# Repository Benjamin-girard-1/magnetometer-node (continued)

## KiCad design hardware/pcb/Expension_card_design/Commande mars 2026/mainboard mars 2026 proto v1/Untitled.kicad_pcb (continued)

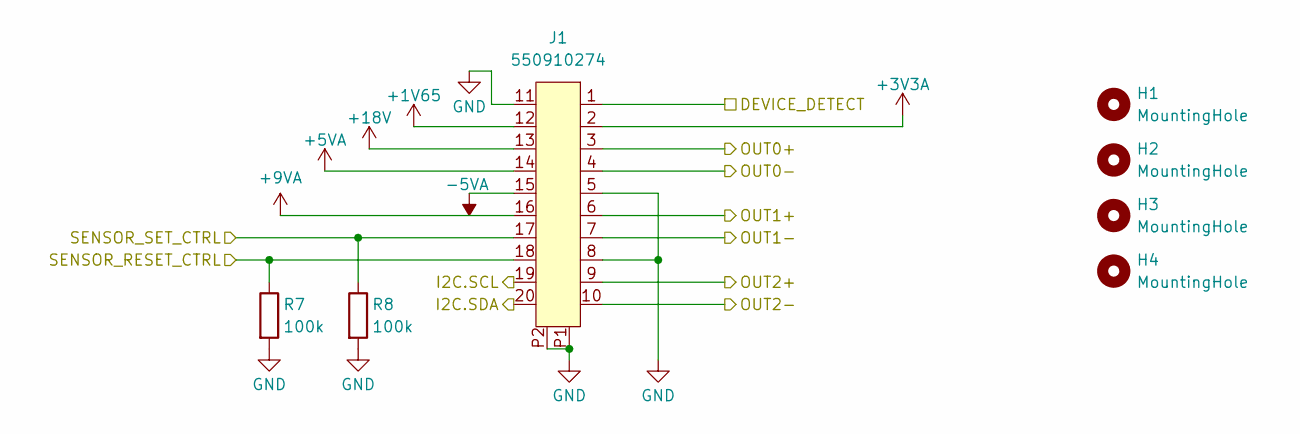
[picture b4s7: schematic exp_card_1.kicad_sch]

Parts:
H1, H2, H3, H4: MountingHole; MountingHole_4.3mm_M4
J1: 550910274; CON_550910274_MOL; LCSC C114095
R7, R8: 100k; R_0603_1608Metric; LCSC C25803

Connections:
+1V65: J1.12; also elsewhere on the board
+3V3A: J1.2; also elsewhere on the board
+5VA: J1.14; also elsewhere on the board
+9VA: J1.16; also elsewhere on the board
+18V: J1.13; also elsewhere on the board
-5VA: J1.15; also elsewhere on the board
/ADC_AD777x/AIN3+: J1.4; also elsewhere on the board
/ADC_AD777x/AIN3-: J1.3; also elsewhere on the board
/ADC_AD777x/AIN4+: J1.7; also elsewhere on the board
/ADC_AD777x/AIN4-: J1.6; also elsewhere on the board
/ADC_AD777x/AIN5+: J1.9; also elsewhere on the board
/ADC_AD777x/AIN5-: J1.10; also elsewhere on the board
/DEVICE_DETECT_2: J1.1; also elsewhere on the board
/RESET_2: J1.18, R7.1; also elsewhere on the board
/SCL_2: J1.19; also elsewhere on the board
/SDA_2: J1.20; also elsewhere on the board
/SET_2: J1.17, R8.1; also elsewhere on the board
GND: J1.5, J1.8, J1.11, J1.P1, J1.P2, R7.2, R8.2; also elsewhere on the board

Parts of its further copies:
H9, H10, H11, H12: MountingHole; MountingHole_4.3mm_M4
J3: 550910274; CON_550910274_MOL; LCSC C114095
R55, R56: 100k; R_0603_1608Metric; LCSC C25803

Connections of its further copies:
+1V65: J3.12; also elsewhere on the board
+3V3A: J3.2; also elsewhere on the board
+5VA: J3.14; also elsewhere on the board
+9VA: J3.16; also elsewhere on the board
+18V: J3.13; also elsewhere on the board
-5VA: J3.15; also elsewhere on the board
/ADC_AD777x/AIN0+: J3.3; also elsewhere on the board
/ADC_AD777x/AIN0-: J3.4; also elsewhere on the board
/ADC_AD777x/AIN1+: J3.7; also elsewhere on the board
/ADC_AD777x/AIN1-: J3.6; also elsewhere on the board
/ADC_AD777x/AIN2+: J3.10; also elsewhere on the board
/ADC_AD777x/AIN2-: J3.9; also elsewhere on the board
/DEVICE_DETECT_1: J3.1; also elsewhere on the board
/RESET_1: J3.18, R55.1; also elsewhere on the board
/SCL_1: J3.19; also elsewhere on the board
/SDA_1: J3.20; also elsewhere on the board
/SET_1: J3.17, R56.1; also elsewhere on the board
GND: J3.5, J3.8, J3.11, J3.P1, J3.P2, R55.2, R56.2; also elsewhere on the board

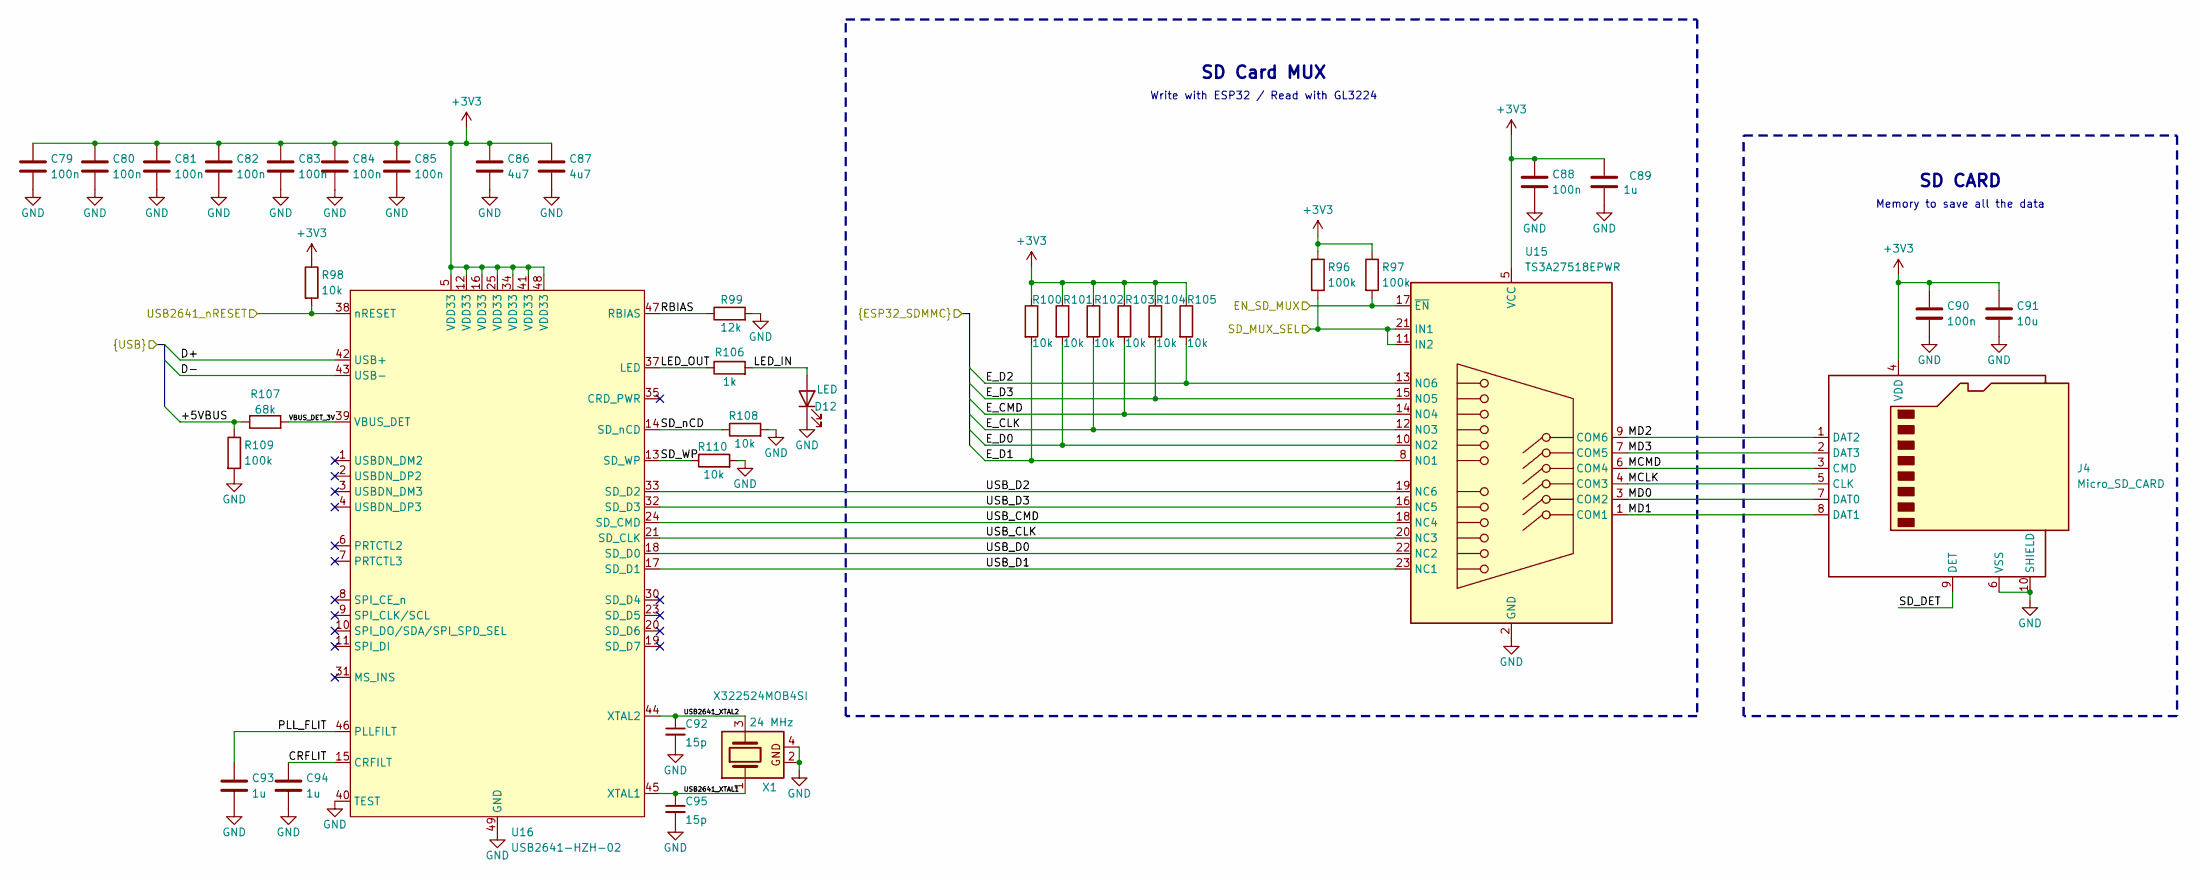
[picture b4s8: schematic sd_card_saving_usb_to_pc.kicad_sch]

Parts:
C79, C80, C81, C82, C83, C84, C85, C88, C90: 100n; C_0603_1608Metric; LCSC C14663
C86, C87: 4u7; C_1206_3216Metric; LCSC C29823
C89, C93, C94: 1u; C_0805_2012Metric; LCSC C28323
C91: 10u; C_0805_2012Metric; LCSC C15850
C92, C95: 15p; C_0603_1608Metric; LCSC C1644
D12: LED; LED_0805_2012Metric; LCSC C2296
J4: Micro_SD_CARD; CONN_503398-1892_MOL; LCSC C428492
R96, R97, R109: 100k; R_0603_1608Metric; LCSC C25803
R98, R100, R101, R102, R103, R104, R105, R108, R110: 10k; R_0603_1608Metric; LCSC C25804
R99: 12k; R_0603_1608Metric; LCSC C22790
R106: 1k; R_0603_1608Metric; LCSC C21190
R107: 68k; R_0603_1608Metric; LCSC C23231
U15: TS3A27518EPWR; TSSOP-24_4.4x7.8mm_P0.65mm; LCSC C2651937
U16: USB2641-HZH-02; QFN-48-1EP_7x7mm_P0.5mm_EP5.3x5.3mm; LCSC C633596
X1: X322524MOB4SI; Crystal_SMD_3225-4Pin_3.2x2.5mm; LCSC C70590

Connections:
+3V3: C79.1, C80.1, C81.1, C82.1, C83.1, C84.1, C85.1, C86.1, C87.1, C88.1, C89.2, C90.1, C91.1, J4.4 (VDD), R96.1, R97.1, R98.1, R100.1, R101.1, R102.1, R103.1, R104.1, R105.1, U15.5 (VCC), U16.5 (VDD33), U16.12 (VDD33), U16.16 (VDD33), U16.25 (VDD33), U16.34 (VDD33), U16.41 (VDD33), U16.48 (VDD33); also elsewhere on the board
/DATA_SAVING/+5VBUS: R107.1, R109.1; also elsewhere on the board
/DATA_SAVING/CRFLIT: C94.1, U16.15 (CRFILT)
/DATA_SAVING/D+: U16.42 (USB+); also elsewhere on the board
/DATA_SAVING/D-: U16.43 (USB-); also elsewhere on the board
/DATA_SAVING/EN_SD_MUX: R97.2, U15.17 (~EN); also elsewhere on the board
/DATA_SAVING/E_CLK: R102.2, U15.12 (NO3); also elsewhere on the board
/DATA_SAVING/E_CMD: R103.2, U15.14 (NO4); also elsewhere on the board
/DATA_SAVING/E_D0: R101.2, U15.10 (NO2); also elsewhere on the board
/DATA_SAVING/E_D1: R100.2, U15.8 (NO1); also elsewhere on the board
/DATA_SAVING/E_D2: R105.2, U15.13 (NO6); also elsewhere on the board
/DATA_SAVING/E_D3: R104.2, U15.15 (NO5); also elsewhere on the board
/DATA_SAVING/LED_IN: D12.2 (A), R106.2
/DATA_SAVING/LED_OUT: R106.1, U16.37 (LED)
/DATA_SAVING/MCLK: J4.5 (CLK), U15.4 (COM3)
/DATA_SAVING/MCMD: J4.3 (CMD), U15.6 (COM4)
/DATA_SAVING/MD0: J4.7 (DAT0), U15.3 (COM2)
/DATA_SAVING/MD1: J4.8 (DAT1), U15.1 (COM1)
/DATA_SAVING/MD2: J4.1 (DAT2), U15.9 (COM6)
/DATA_SAVING/MD3: J4.2 (DAT3), U15.7 (COM5)
/DATA_SAVING/PLL_FLIT: C93.1, U16.46 (PLLFILT)
/DATA_SAVING/RBIAS: R99.1, U16.47 (RBIAS)
/DATA_SAVING/SD_DET: J4.9 (DET)
/DATA_SAVING/SD_MUX_SEL: R96.2, U15.11 (IN2), U15.21 (IN1); also elsewhere on the board
/DATA_SAVING/SD_WP: R110.1, U16.13 (SD_WP)
/DATA_SAVING/SD_nCD: R108.1, U16.14 (SD_nCD)
/DATA_SAVING/USB2641_XTAL1: C95.1, U16.45 (XTAL1), X1.1
/DATA_SAVING/USB2641_XTAL2: C92.1, U16.44 (XTAL2), X1.3
/DATA_SAVING/USB2641_nRESET: R98.2, U16.38 (nRESET); also elsewhere on the board
/DATA_SAVING/USB_CLK: U15.20 (NC3), U16.21 (SD_CLK)
/DATA_SAVING/USB_CMD: U15.18 (NC4), U16.24 (SD_CMD)
/DATA_SAVING/USB_D0: U15.22 (NC2), U16.18 (SD_D0)
/DATA_SAVING/USB_D1: U15.23 (NC1), U16.17 (SD_D1)
/DATA_SAVING/USB_D2: U15.19 (NC6), U16.33 (SD_D2)
/DATA_SAVING/USB_D3: U15.16 (NC5), U16.32 (SD_D3)
/DATA_SAVING/VBUS_DET_3V: R107.2, U16.39 (VBUS_DET)
GND: C79.2, C80.2, C81.2, C82.2, C83.2, C84.2, C85.2, C86.2, C87.2, C88.2, C89.1, C90.2, C91.2, C92.2, C93.2, C94.2, C95.2, D12.1 (K), J4.6 (VSS), J4.10 (SHIELD), J4.11 (VSS), J4.12 (VSS), J4.13 (VSS), J4.14 (VSS), R99.2, R108.2, R109.2, R110.2, U15.2 (GND), U16.40 (TEST), U16.49 (GND), X1.2, X1.4; also elsewhere on the board

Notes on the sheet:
SD CARD
SD Card MUX
Memory to save all the data
Write with ESP32 / Read with GL3224

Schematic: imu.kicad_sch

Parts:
C96, C97, C98, C99, C100, C101: 100n; C_0603_1608Metric; LCSC C14663
TP3, TP4: TestPoint; TestPoint_THTPad_1.0x1.0mm_Drill0.5mm; not fitted
U17: SCL3300-D01-10; SCL3300-D01-10_MUR; LCSC C3825395
U19: LSM6DSVETR; LGA-14_3x2.5mm_P0.5mm_LayoutBorder3x4y; LCSC C41785564

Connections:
+3V3: C96.2, C97.2, C100.2, C101.2, U17.4 (VDD), U17.9 (DVIO), U19.5 (VDD_IO), U19.8 (VDD); also elsewhere on the board
/IMU/CS_LSM: U19.12 (CS); also elsewhere on the board
/IMU/CS_SCL: U17.5 (CS); also elsewhere on the board
/IMU/MISO: U17.6 (MISO), U19.1 (SDO); also elsewhere on the board
/IMU/MOSI: U17.7 (MOSI), U19.14 (SDA); also elsewhere on the board
/IMU/SCLK: U17.8 (SCK), U19.13 (SCL); also elsewhere on the board
GND: C96.1, C97.1, C98.1, C99.1, C100.1, C101.1, U17.1 (AVSS), U17.3 (RESERVED), U17.11 (DVSS), U17.12 (EMC_GND), U19.2 (SDx), U19.3 (SCx), U19.6 (GND), U19.7 (GND); also elsewhere on the board
unnamed: C99.2, U17.2 (A_EXTC)
unnamed: C98.2, U17.10 (D_EXTC)
unnamed: TP4.1, U19.4 (INT1)
unnamed: TP3.1, U19.9 (INT2)

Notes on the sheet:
Inertial Measurement Unit (IMU)
To know the orientation of the device

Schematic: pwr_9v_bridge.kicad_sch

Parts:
C4: 22p; C_0603_1608Metric; LCSC C1653
C5: 1u; C_0805_2012Metric; LCSC C28323
C6, C9, C10: 4u7; C_1206_3216Metric; LCSC C29823
C7: 10u; C_0805_2012Metric; LCSC C15850
C8: 100n; C_0603_1608Metric; LCSC C14663
D2: SS34; D_SMA; LCSC C8678
L2: 10u; L_Sunlord_MWSA0503S; LCSC C177248
R9, R10, R11, R15: 0; R_1206_3216Metric; LCSC C17888; not fitted
R12: 510k; R_0603_1608Metric; LCSC C23192
R13: 1k; R_0603_1608Metric; LCSC C21190
R14: 200k; R_0603_1608Metric; LCSC C25811
R16: 90k9; R_1206_3216Metric; LCSC C870933
R17: 100k; R_0603_1608Metric; LCSC C25803
TP13, TP14: TestPoint; TestPoint_THTPad_1.0x1.0mm_Drill0.5mm; not fitted
U2: LT3042xMSE; MSOP-10-1EP_3x3mm_P0.5mm_EP1.68x1.88mm; LCSC C580009
U3: TPS61040DBV; SOT-23-5; LCSC C7722

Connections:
+5V: R15.1; also elsewhere on the board
+9VA: R11.2; also elsewhere on the board
/MCU_ESP32S3/EN_BST_10V: U3.4 (EN); also elsewhere on the board
/PWR_9V_BRIDGE/+5V_IN_BST: C10.1, L2.1, R15.2, U3.5 (VIN)
/PWR_9V_BRIDGE/+9V_LDO_OUT: C6.1, R11.1, TP14.1, U2.9 (OUTS), U2.10 (OUT)
/PWR_9V_BRIDGE/+10V: R9.2, R10.1; also elsewhere on the board
/PWR_9V_BRIDGE/+10V_LDO_IN: C7.1, C8.1, R10.2, U2.1 (IN), U2.2 (IN), U2.3 (EN/UV), U2.6 (PGFB)
/PWR_9V_BRIDGE/+10V_OUT: C4.1, C5.1, D2.1 (K), R9.1, R12.1, TP13.1
/PWR_9V_BRIDGE/BST_10V_FB: C4.2, R14.2, R17.1, U3.3 (FB)
/PWR_9V_BRIDGE/BST_10V_FB_DIV: R12.2, R14.1
/PWR_9V_BRIDGE/BST_10V_SW: D2.2 (A), L2.2, U3.1 (SW)
/PWR_9V_BRIDGE/LDO_9V_ILIM: R13.2, U2.5 (ILIM)
/PWR_9V_BRIDGE/LDO_9V_SET: C9.1, R16.1, U2.7 (SET)
GND: C5.2, C6.2, C7.2, C8.2, C9.2, C10.2, R13.1, R16.2, R17.2, U2.8 (GND), U2.11 (GND), U3.2 (GND); also elsewhere on the board

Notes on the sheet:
Voltage for bridge of the magnetic sensors
+9V LDO
Voltage for the +9V and +5V LDO
+10V Boost

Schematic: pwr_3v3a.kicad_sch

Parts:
C32, C35: 4u7; C_1206_3216Metric; LCSC C29823
C33, C34: 100n; C_0603_1608Metric; LCSC C14663
FB1: FerriteBead; L_0603_1608Metric; LCSC C14709
R53, R54: 0; R_1206_3216Metric; LCSC C17888; not fitted
TP12: TestPoint; TestPoint_THTPad_1.0x1.0mm_Drill0.5mm; not fitted
U10: TPS7A2033PDBVR; SOT-23-5; LCSC C2862740

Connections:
+3V3A: R54.2; also elsewhere on the board
+5V: R53.1; also elsewhere on the board
/MCU_ESP32S3/EN_LDO_3V3: U10.3 (EN); also elsewhere on the board
/PWR_3V3A/+5V_IN: FB1.1, R53.2
/PWR_3V3A/LDO_3V3_IN: C32.1, C33.1, FB1.2, U10.1 (IN)
/PWR_3V3A/LDO_3V3_OUT: C34.1, C35.1, R54.1, TP12.1, U10.5 (OUT)
GND: C32.2, C33.2, C34.2, C35.2, U10.2 (GND), U10.4 (NC); also elsewhere on the board

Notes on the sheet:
+3.3V LDO
Voltage for analog domain of the ADC

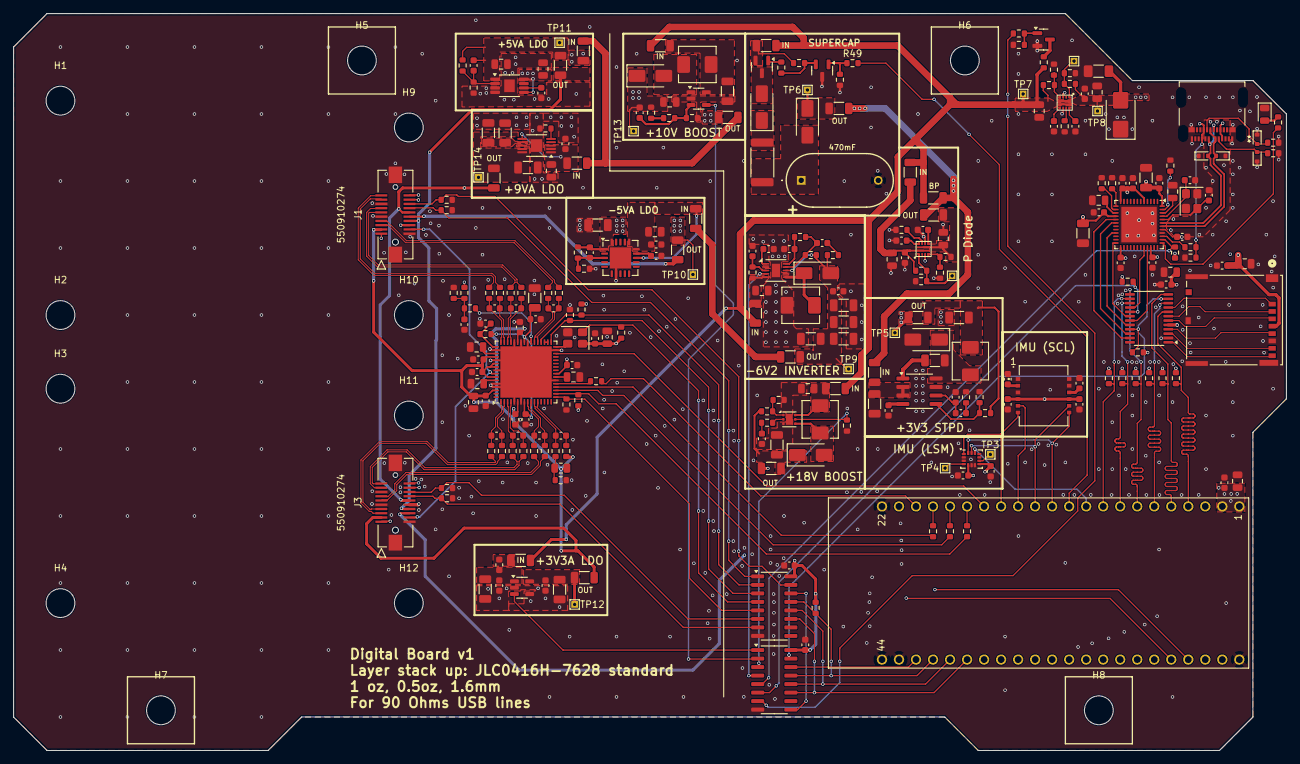
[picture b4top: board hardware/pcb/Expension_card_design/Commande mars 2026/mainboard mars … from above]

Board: 4 copper layers, 190.0 x 110.0 mm, 282 parts (0 on the bottom side), 191 nets.

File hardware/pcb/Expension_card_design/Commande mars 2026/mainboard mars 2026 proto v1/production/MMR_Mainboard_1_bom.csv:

Designator,Footprint,Quantity,Value,LCSC Part #
"C1, C13, C17, C23, C36, C51, C60, C62, C66, C7, C72, C91",0805,12,10u,C15850
"C10, C2, C32, C35, C6, C74, C75, C76, C77, C86, C87, C9",1206,12,4u7,C29823
"C100, C101, C11, C12, C14, C16, C21, C33, C34, C37, C38, C39, C40, C41, C42, C43, C50, C53, C54, C56, C64, C67, C71, C79, C8, C80, C81, C82, C83, C84, C85, C88, C90, C96, C97, C98, C99",0603,37,100n,C14663
"C15, C20, C5, C57, C58, C59, C89, C93, C94",0805,9,1u,C28323
"C18, C28, C29, C3, C61, C63, C68, C73",0603,8,10n,C57112
"C19, C30, C44, C45, C47, C48, C49, C52",0603,8,1n,C1588
"C22, C24",1206,2,22u,C12891
"C25, C55, C69",1206,3,47u,C96123
"C26, C78",0603,2,4n7,C53987
"C27, C70",0603,2,10p,C1634
C4,0603,1,22p,C1653
"C46, C65",0603,2,220n,C21120
"C92, C95",0603,2,15p,C1644
"D1, D10, D11, D2, D8, D9",D_SMA,6,SS34,C8678
D12,0805,1,LED,C2296
D3,D_SMB,1,P6SMB6.8CA,C7420377
"D4, D5, D6, D7",D_SOD-523,4,H5VUD5BB,C20615820
FB1,0603,1,FerriteBead,C14709
"J1, J3",CON_550910274_MOL,2,550910274,C114095
J2,CONN_201267-0005_MOL,1,USB_C_RECEPTACLE_MOLEX,C565324
J4,CONN_503398-1892_MOL,1,Micro_SD_CARD,C428492
"L1, L2, L3, L4",L_Sunlord_MWSA0503S,4,10u,C177248
"Q1, Q3",SOT-23,2,AO3400A,C20917
Q2,SOT-23,1,AO3401A,C15127
"R100, R101, R102, R103, R104, R105, R108, R110, R18, R43, R5, R61, R98",0603,13,10k,C25804
"R106, R13, R58, R65, R69, R81",0603,6,1k,C21190
R107,0603,1,68k,C23231
"R109, R17, R23, R32, R38, R4, R52, R55, R56, R59, R7, R73, R76, R78, R8, R80, R88, R91, R94, R96, R97",0603,21,100k,C25803
"R12, R93",0603,2,510k,C23192
"R14, R24, R40",0603,3,200k,C25811
R16,1206,1,90k9,C870933
"R19, R20, R21, R60, R62, R63, R64, R66, R68, R70, R71, R72, R74, R75, R77, R79",0603,16,22,C23345
"R22, R37",0603,2,470k,C23178
"R25, R41, R47, R84",0603,4,39k,C23153
"R27, R45",0603,2,2k,C22975
"R28, R29",0603,2,5k1,C23186
R3,0603,1,49k9,C23184
"R30, R31, R48, R49",0603,4,100,C22775
R42,0603,1,75k,C23242
R44,0603,1,24k,C23352
R50,2512,1,22,C2974113
R57,0603,1,300k,C23024
R6,0603,1,3k6,C22980
R67,0805,1,27k,C17526
"R85, R99",0603,2,12k,C22790
R89,0603,1,330k,C23137
R90,0603,1,10,C22859
TH1,0603,1,NCU18XH103D6SRB,C3154835
U1,WSON-6-1EP_2x2mm_P0.65mm_EP1x1.6mm,1,TPS61170,C15163
U10,SOT-23-5,1,TPS7A2033PDBVR,C2862740
U11,QFN-64-1EP_9x9mm_P0.5mm_EP7.65x7.65mm,1,AD7779ACPZ,C398822
U12,HVSSOP-8-1EP_3x3mm_P0.65mm_EP1.57x1.89mm,1,TPS7A4901DGNR,C16430
U13,Texas_RGW0020A_VQFN-20-1EP_5x5mm_P0.65mm_EP3.15x3.15mm,1,TPS7A3301RGWR,C90082
U14,VSON-10-1EP_3x3mm_P0.5mm_EP1.2x2mm,1,TPS63700DRCR,C54792
U15,TSSOP-24_4.4x7.8mm_P0.65mm,1,TS3A27518ERTW,C2651937
U16,QFN-48-1EP_7x7mm_P0.5mm_EP5.3x5.3mm,1,USB2641-HZH-02,C633596
U17,SCL3300-D01-10_MUR,1,SCL3300-D01-10,C3825395
U19,LGA-14_3x2.5mm_P0.5mm_LayoutBorder3x4y,1,LSM6DSVETR,C41785564
U2,MSOP-10-1EP_3x3mm_P0.5mm_EP1.68x1.88mm,1,LT3042xMSE,C580009
U3,SOT-23-5,1,TPS61040DBV,C7722
"U4, U5",SOIC-16_3.9x9.9mm_P1.27mm,2,"74HC595D,118",C5947
"U7, U8",SMD_VQFN-HR-10,2,TPS25210LRPWR,C2861226
U9,SOIC-8_3.9x4.9mm_P1.27mm,1,TPS54331DR,C9865
X1,Crystal_SMD_3225-4Pin_3.2x2.5mm,1,X322524MOB4SI,C70590
Y1,Crystal_SMD_3225-4Pin_3.2x2.5mm,1,OT2JI-111-8.192M,C7425393

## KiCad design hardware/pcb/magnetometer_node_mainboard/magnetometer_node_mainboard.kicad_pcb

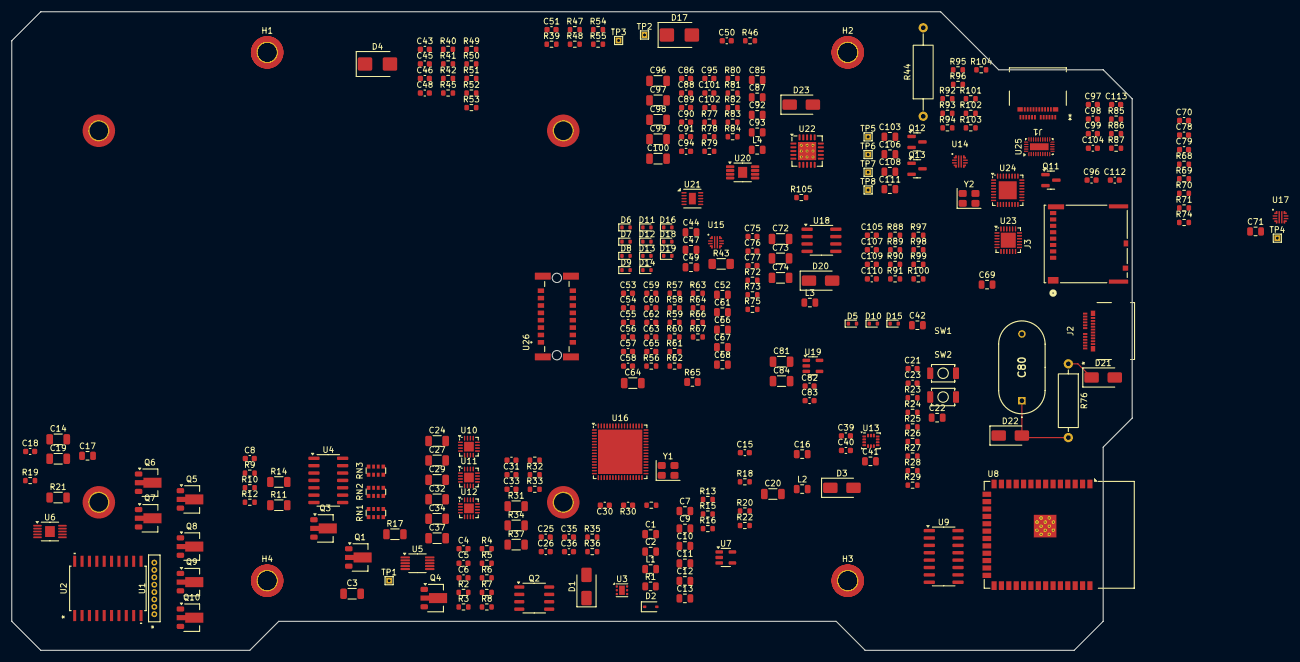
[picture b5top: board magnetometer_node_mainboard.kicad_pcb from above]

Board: 2 copper layers, 193.0 x 110.0 mm, 318 parts (0 on the bottom side), 220 nets.

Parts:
C1, C2, C7, C9, C10, C11, C12, C13, C17, C22, C41, C44, C49, C52, C61, C71, C85, C87, C92, C93, C106: 10u; C_0805_2012Metric
C3, C14, C19, C20, C24, C27, C29, C32, C34, C37, C81, C84, C97#2, C98, C99#2, C100: 4u7; C_1206_3216Metric
C4, C26, C31, C36, C62, C90: 220n; C_0603_1608Metric
C5, C46, C51, C79: 1n; C_0603_1608Metric
C6, C45, C50, C77, C78, C86, C88, C95: 10n; C_0603_1608Metric
C8, C18, C21, C23, C25, C28, C30, C33, C35, C38, C39, C40, C43, C48, C53, C54, C55, C56, C57, C58, C59, C60, C63, C65, C70, C82, C83, C89, C94, C96, C97, C98#2, C99, C102, C104, C105, C107, C109, C110: 100n; C_0603_1608Metric
C15: 22p; C_0603_1608Metric
C16, C42, C47, C66, C67, C68, C69, C103, C108, C111: 1u; C_0805_2012Metric
C64, C74, C96#2: 47u; C_1206_3216Metric
C72, C73: 22u; C_1206_3216Metric
C75, C91: 10p; C_0603_1608Metric
C76, C101: 4n7; C_0603_1608Metric
C80: 470mF; C_Radial_D8.0mm_P11.50mm
C112, C113: 18p; C_0603_1608Metric
D1, D3, D20, D21, D22, D23: SS34; D_SMA
D2: 1N4148WS; D_SOD-323
D4, D17: P6SMB6.8CA; D_SMB
D5, D6, D7, D8, D9, D10, D11, D12, D13, D14, D15, D16, D18, D19: H5VUD5BB; D_SOD-523
H1, H2, H3, H4, H5, H5#2, H6, H6#2, H7, H7#2, H8, H8#2: MountingHole_Pad; MountingHole_3.2mm_M3_DIN965_Pad_TopBottom
J1, J2: USB_C_RECEPTACLE_MOLEX; CONN_201267-0005_MOL
J3: Micro_SD_CARD; CONN_503398-1892_MOL
L1, L2, L3, L4: 10u; C_0805_2012Metric
Q1, Q4, Q5, Q7, Q9: D882; SOT-89-3
Q2: DMC3028LSD; SO-8_3.9x4.9mm_P1.27mm
Q3, Q6, Q8, Q10: B772; SOT-89-3
Q11, Q13: AO3400A; SOT-23
Q12: AO3401A; SOT-23
R1: 220; R_0805_2012Metric
R2, R4, R8, R30, R32, R33, R35, R36, R38, R59, R62, R64, R67: 1k; R_0603_1608Metric
R3: 49k9; R_0603_1608Metric
R5, R22, R40, R47, R53, R57, R60, R61, R63, R66, R69, R79, R82, R84, R89, R97, R98, R99, R100, R101, R103, R104: 100k; R_0603_1608Metric
R6, R23, R24, R28, R29, R73, R90, R91, R92, R93, R94: 10k; R_0603_1608Metric
R7: 3k6; R_0603_1608Metric
R9, R10, R12, R13, R15, R16, R51, R52, R86, R88: 100; R_0603_1608Metric
R11, R14, R17: 20; R_1206_3216Metric
R18, R81: 510k; R_0603_1608Metric
R19, R45, R50, R74, R95, R96: 2k; R_0603_1608Metric
R20, R41, R48, R70: 200k; R_0603_1608Metric
R21: 90k9; R_1206_3216Metric
R25, R26, R27, R56: 22; R_0603_1608Metric
R31, R34, R37: 48,7; R_1206_3216Metric
R39, R46, R68: 470k; R_0603_1608Metric
R42, R49, R71, R77, R85: 39k; R_0603_1608Metric
R43: R_1206_3216Metric_Pad1.30x1.75mm_HandSolder
R44: R_Axial_DIN0309_L9.0mm_D3.2mm_P15.24mm_Horizontal
R54, R55: 5k1; R_0603_1608Metric
R58: 300k; R_0603_1608Metric
R65: 2k4; R_0805_2012Metric
R72: 75k; R_0603_1608Metric
R75: 24k; R_0603_1608Metric
R76: 47; R_Axial_DIN0309_L9.0mm_D3.2mm_P12.70mm_Horizontal
R78: 12k; R_0603_1608Metric
R80: 10; R_0603_1608Metric
R83, R87: 330k; R_0603_1608Metric
R102: 680; R_0603_1608Metric
R105: 900k; R_0603_1608Metric
RN1, RN2, RN3: 10k; R_Array_Convex_4x0612
SW1, SW2: TS-1088-AR02016
TP1, TP2, TP3, TP4: TestPoint; TestPoint_THTPad_1.0x1.0mm_Drill0.5mm
TP5: GL3224_SPI_CS; TestPoint_THTPad_1.0x1.0mm_Drill0.5mm
TP6: GL3224_SPI_CK; TestPoint_THTPad_1.0x1.0mm_Drill0.5mm
TP7: GL3224_SPI_MISO; TestPoint_THTPad_1.0x1.0mm_Drill0.5mm
TP8: GL3224_SPI_MOSI; TestPoint_THTPad_1.0x1.0mm_Drill0.5mm
U1: HMC1001-RC; SIP8_HMC1001_HNW
U2: HMC1002-TR; SOIC20_HNW
U3: TPS61170; WSON-6-1EP_2x2mm_P0.65mm_EP1x1.6mm
U4: LM324; SOIC-14_3.9x8.7mm_P1.27mm
U5: MCP4728; MSOP-10_3x3mm_P0.5mm
U6: LT3042xMSE; MSOP-10-1EP_3x3mm_P0.5mm_EP1.68x1.88mm
U7: TPS61040DBV; SOT-23-5
U8: ESP32-S3-WROOM-1
U9: 74HC595D,118; SOIC-16_3.9x9.9mm_P1.27mm
U10, U11, U12: INA851RGTR; VQFN-16-1EP_3x3mm_P0.5mm_EP1.68x1.68mm
U13: ISM330DHCXTR; LGA-14_3x2.5mm_P0.5mm_LayoutBorder3x4y
U14, U15, U17: TPS25210LRPWR; VQFN-HR-10
U16: AD7779; QFN-64-1EP_9x9mm_P0.5mm_EP7.65x7.65mm
U18: TPS54331DR; SOIC-8_3.9x4.9mm_P1.27mm
U19: TPS7A2033PDBVR; SOT-23-5
U20: TPS7A4901DGNR; HVSSOP-8-1EP_3x3mm_P0.65mm_EP1.57x1.89mm
U21: TPS63700DRCR; VSON-10-1EP_3x3mm_P0.5mm_EP1.2x2mm
U22: TPS7A3301RGWR; Texas_RGW0020A_VQFN-20-1EP_5x5mm_P0.65mm_EP3.15x3.15mm_Ther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
U23: TS3A27518ERTW; WQFN-24-1EP_4x4mm_P0.5mm_EP2.6x2.6mm
U24: GL3224-OIY04; QFN-32-1EP_5x5mm_P0.5mm_EP3.1x3.1mm
U25: HD3SS3220RNHR; Texas_RNH0030A_WQFN-30-1EP_2.5x4.5mm_P0.4mm_EP1.2x3.2mm
U26: 2x08_pheonix_connector_male; GPS_TILE_3D
Y1: OT2JI-111-8.192M; Crystal_SMD_3225-4Pin_3.2x2.5mm
Y2: X322525MOB4SI; Crystal_SMD_3225-4Pin_3.2x2.5mm

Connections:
+1V65: U10.13 (VOCM), U11.13 (VOCM), U12.13 (VOCM), U16.57 (VCM)
+3V3: C21.1, C22.1, C23.1, C39.1, C40.1, C41.1, C58.1, C60.1, C61.1, C74.1, C105.1, C106.1, C107.1, C108.2, C109.1, J3.4 (VDD), L3.2, R23.1, R24.1, R28.2, R29.2, R63.1, R66.1, R72.1, R90.1, R91.1, R92.1, R93.1, R94.1, R95.1, R99.1, R100.1, R101.1, U8.2 (3V3), U9.16 (VCC), U13.5 (VDDIO), U13.8 (VDD), U13.12 (CS), U14.3 (PG), U15.3 (PG), U16.24 (IOVDD), U16.54 (FORMAT1), U16.55 (FORMAT0), U17.3 (PG), U23.5 (VCC), U25.8 (VCC33), U26.A1, U26.A2, U26.A3, U26.A4, Y1.4 (VDD)
+3V3A: C52.1, C53.1, C54.1, C55.1, C56.1, C57.1, C83.1, C84.1, R62.1, U10.16 (VCLAMP+), U11.16 (VCLAMP+), U12.16 (VCLAMP+), U16.6 (AVDD1A), U16.43 (AVDD1B), U16.52 (AVDD2B), U16.58 (AVDD2A), U16.62 (AVDD4), U19.1 (OUT)
+3V3D: C8.1, U5.1 (VDD)
+5V: C2.1, C20.1, C44.1, C49.1, C69.1, C70.1, C92.1, C110.1, C111.2, D21.2 (A), L1.1, L2.1, Q5.2, Q7.2, Q9.2, Q12.2 (S), R40.1, R47.1, R51.1, R68.1, R80.2, R85.1, U3.6 (VIN), U4.4 (V+), U7.5 (VIN), U14.6 (OUT), U15.6 (OUT), U17.5 (IN), U21.5 (IN), U25.30 (VDD5)
+5VA: C24.1, C25.1, C27.1, C28.1, C32.1, C33.1, C86.1, C87.1, R77.1, U10.14 (VS+), U11.14 (VS+), U12.14 (VS+), U20.1 (OUT)
+9VA: C14.1, R58.1, U1.7 (VBRIDGE), U2.4 (VBRIDGE(A)), U2.11 (VBRIDGE(B)), U6.9 (OUTS), U6.10 (OUT)
+18V: C3.1, D1.1 (K), R1.2, R3.1
-5VA: C29.1, C30.1, C34.1, C35.1, C37.1, C38.1, C95.1, C96#2.1, Q6.2, Q8.2, Q10.2, R83.1, U4.11 (V-), U10.7 (VS-), U11.7 (VS-), U12.7 (VS-), U22.1 (OUT), U22.20 (OUT)
/ADC_AD777X/ADC_9VA_MON: C59.1, R58.2, R59.1, R60.1
/ADC_AD777X/ADC_9VA_MON_FLT: R59.2, U16.39 (AIN6+)
/ADC_AD777X/ADC_AREG1CAP: C67.1, U16.59 (AREG1CAP)
/ADC_AD777X/ADC_AREG2CAP: C68.1, U16.51 (AREG2CAP)
/ADC_AD777X/ADC_CONVST_SAR: R57.1, U8.11 (IO18), U16.17 (CONVST_SAR)
/ADC_AD777X/ADC_DRDY: U8.39 (IO1), U16.30 (~DRDY)
/ADC_AD777X/ADC_DREGCAP: C66.1, U16.23 (DREGCAP)
/ADC_AD777X/ADC_MCLK: U16.32 (XTAL2/MCLK), Y1.3 (OUT)
/ADC_AD777X/ADC_MCLK_EN: R66.2, U8.36 (RXD0), Y1.1 (Tri-State)
/ADC_AD777X/ADC_REF+: C63.1, C64.1, R67.1, U16.8 (REF1+), U16.41 (REF2+)
/ADC_AD777X/ADC_REF_OUT: C65.1, R67.2, U16.49 (REF_OUT)
/ADC_AD777X/ADC_RESET: R63.2, U8.10 (IO17), U16.36 (~RESET)
/ADC_AD777X/ADC_SDO: R56.1, U16.21 (DCLK0/SDO)
/ADC_AD777X/ADC_START: R61.1, U8.37 (TXD0), U16.33 (~START)
/ADC_AD777X/PT1000_AIN+: C62.1, R62.2, U16.37 (AIN7+)
/ADC_AD777X/PT1000_AIN-: C62.2, R64.2, U16.38 (AIN7-)
/ADC_AD777X/PT1000_DRAIN: R64.1, R65.1
/ADC_AD777X/SPI.CS: R25.1, U16.18 (ALERT/~CS)
/ADC_AD777X/SPI.SCLK: R26.1, U16.19 (DCLK2/SCLK)
/ADC_AD777X/SPI.SDI: R27.1, U16.20 (DCLK1/SDI)
/ADC_AD777X/SPI.SDO: R56.2, U8.7 (IO7)
/ADC_AD777X/X_INA_OUT+: C26.1, R30.2, U16.2 (AIN0+)
/ADC_AD777X/X_INA_OUT-: C26.2, R32.2, U16.1 (AIN0-)
/ADC_AD777X/Y_INA_OUT+: C36.1, R36.2, U16.4 (AIN1+)
/ADC_AD777X/Y_INA_OUT-: C36.2, R38.2, U16.3 (AIN1-)
/ADC_AD777X/Z_INA_OUT+: C31.1, R33.2, U16.10 (AIN2+)
/ADC_AD777X/Z_INA_OUT-: C31.2, R35.2, U16.9 (AIN2-)
/ANALOG_FRONTEND_INA851/BR_X+: U2.2 (OUT+(A)), U10.1 (IN-)
/ANALOG_FRONTEND_INA851/BR_X-: U2.5 (OUT-(A)), U10.4 (IN+)
/ANALOG_FRONTEND_INA851/BR_Y+: U2.9 (OUT+(B)), U12.4 (IN+)
/ANALOG_FRONTEND_INA851/BR_Y-: U2.12 (OUT-(B)), U12.1 (IN-)
/ANALOG_FRONTEND_INA851/BR_Z+: U1.8 (OUT-), U11.4 (IN+)
/ANALOG_FRONTEND_INA851/BR_Z-: U1.5 (OUT+), U11.1 (IN-)
/ANALOG_FRONTEND_INA851/X_INA_PRE_AAF+: R30.1, U10.11 (OUT+)
/ANALOG_FRONTEND_INA851/X_INA_PRE_AAF-: R32.1, U10.10 (OUT-)
/ANALOG_FRONTEND_INA851/X_RG+: R31.1, U10.2 (RG+)
/ANALOG_FRONTEND_INA851/X_RG-: R31.2, U10.3 (RG-)
/ANALOG_FRONTEND_INA851/Y_INA_PRE_AAF+: R36.1, U12.11 (OUT+)
/ANALOG_FRONTEND_INA851/Y_INA_PRE_AAF-: R38.1, U12.10 (OUT-)
/ANALOG_FRONTEND_INA851/Y_RG+: R37.1, U12.2 (RG+)
/ANALOG_FRONTEND_INA851/Y_RG-: R37.2, U12.3 (RG-)
/ANALOG_FRONTEND_INA851/Z_INA_PRE_AAF+: R33.1, U11.11 (OUT+)
/ANALOG_FRONTEND_INA851/Z_INA_PRE_AAF-: R35.1, U11.10 (OUT-)
/ANALOG_FRONTEND_INA851/Z_RG+: R34.1, U11.2 (RG+)
/ANALOG_FRONTEND_INA851/Z_RG-: R34.2, U11.3 (RG-)
/DATA_SAVING/+5VBUS_DATA: C42.1, C43.1, D4.2 (A2), J1.A4 (VBUS), J1.A9 (VBUS), J1.B4 (VBUS), J1.B9 (VBUS), R39.1, R43.2, R44.1, R105.1, U14.5 (IN)
/DATA_SAVING/+5VBUS_DET: R105.2, U25.5 (VBUS_DET)
/DATA_SAVING/CC1: D6.2, J1.A5 (CC1), U25.2 (CC1)
/DATA_SAVING/CC2: D5.2, J1.B5 (CC2), U25.1 (CC2)
/DATA_SAVING/CLK: U8.32 (IO39), U23.22 (NC2)
/DATA_SAVING/CMD: U8.31 (IO38), U23.23 (NC1)
/DATA_SAVING/D0: U8.33 (IO40), U23.20 (NC3)
/DATA_SAVING/D1: U8.34 (IO41), U23.18 (NC4)
/DATA_SAVING/D2: U8.35 (IO42), U23.16 (NC5)
/DATA_SAVING/D3: U8.26 (IO45), U23.19 (NC6)
/DATA_SAVING/D+: D16.2, D19.2, J1.A6 (D+), J1.B6 (D+), J2.A6 (D+), J2.B6 (D+), U8.14 (USB_D+), U24.32 (DP)
/DATA_SAVING/D-: D15.2, D18.2, J1.A7 (D-), J1.B7 (D-), J2.A7 (D-), J2.B7 (D-), U8.13 (USB_D-), U24.31 (DM)
/DATA_SAVING/EN_SD_MUX: R98.1, U9.5 (QF), U23.17 (~EN)
/DATA_SAVING/EN_USB_READ: R88.1, R97.1, U9.6 (QG), U23.11 (IN2), U23.21 (IN1)
/DATA_SAVING/RX1+: D9.2, J1.B11 (RX1+), U25.15 (RX1p)
/DATA_SAVING/RX1-: D10.2, J1.B10 (RX1-), U25.14 (RX1n)
/DATA_SAVING/RX2+: D7.2, J1.A11 (RX2+), U25.18 (RX2p)
/DATA_SAVING/RX2-: D8.2, J1.A10 (RX2-), U25.19 (RX2n)
/DATA_SAVING/TX1+: D14.2, J1.A2 (TX1+), U25.17 (TX1p)
/DATA_SAVING/TX1-: D13.2, J1.A3 (TX1-), U25.16 (TX1n)
/DATA_SAVING/TX2+: D12.2, J1.B2 (TX2+), U25.21 (TX2p)
/DATA_SAVING/TX2-: D11.2, J1.B3 (TX2-), U25.20 (TX2n)
/GPS_TILE/GPS_NRESET: U9.4 (QE), U26.B1
/GPS_TILE/GPS_TIMEPULSE: U8.8 (IO15), U26.B2
/GPS_TILE/GPS_UART.RX: U8.16 (IO46), U26.B4
/GPS_TILE/GPS_UART.TX: U8.24 (IO47), U26.B5
/IMU/I2C.SCL: U5.2 (SCL), U8.38 (IO2), U13.13 (SCL)
/IMU/I2C.SDA: U5.3 (SDA), U8.4 (IO4), U13.14 (SDA)
/IMU/I2C.SDO: U8.15 (IO3), U13.1 (SDO/SA0)
/IO_CONNECTOR/+5VBUS_DEBUG: C47.1, C48.1, D17.2 (A2), J2.A4 (VBUS), J2.A9 (VBUS), J2.B4 (VBUS), J2.B9 (VBUS), R46.1, U15.5 (IN)
/IO_CONNECTOR/EN_KEEPALIVE: R52.1, U8.25 (IO48)
/IO_CONNECTOR/EN_KEEPALIVE_DRAIN: Q11.3 (D), R51.2
/IO_CONNECTOR/EN_KEEPALIVE_GATE: Q11.1 (G), R52.2, R53.1
/MCU_ESP32S3/ADC_SPI_CS: R25.2, U8.5 (IO5)
/MCU_ESP32S3/ADC_SPI_SCLK: R26.2, U8.6 (IO6)
/MCU_ESP32S3/ADC_SPI_SDI: R27.2, U8.12 (IO8)
/MCU_ESP32S3/DAC_LDAC_N: U5.4 (~LDAC), U9.7 (QH)
/MCU_ESP32S3/EN_BST_10V: U7.4 (EN), U9.15 (QA)
/MCU_ESP32S3/EN_BST_18V: R5.1, U3.5 (CTRL), U9.3 (QD)
/MCU_ESP32S3/EN_INV_-5V: U9.2 (QC), U21.4 (EN)
/MCU_ESP32S3/EN_LDO_3V3: U9.1 (QB), U19.3 (EN)
/MCU_ESP32S3/ESP32_BOOTH: R24.2, SW2.2, U8.27 (IO0)
/MCU_ESP32S3/ESP32_EN: R23.2, SW1.2, U8.3 (EN)
/MCU_ESP32S3/SENSOR_RESET_CTRL: Q2.2 (G1), U8.17 (IO9)
/MCU_ESP32S3/SENSOR_SET_CTRL: C5.1, R8.1, U8.18 (IO10)
/PWR_3V3A/LDO_3V3_IN: C81.1, C82.1, U19.4 (IN)
/PWR_3V3D/3V3D_EFUSE_DVDT: C79.1, U17.7 (dV/dt)
/PWR_3V3D/3V3D_EFUSE_EN_ULVO: R68.2, R70.1, TP4.1, U17.1 (EN/ULVO)
/PWR_3V3D/3V3D_EFUSE_ILM: R74.1, U17.9 (ILM)
/PWR_3V3D/3V3D_EFUSE_ITIMER: C78.1, U17.10 (ITIMER)
/PWR_3V3D/3V3D_EFUSE_PGTH: R69.2, R71.1, U17.4 (PGTH)
/PWR_3V3D/5V_CAP_CHG: D21.1 (K), R76.1
/PWR_3V3D/5V_HOLDUP: C71.1, C73.1, D22.1 (K), R69.1, U17.6 (OUT), U18.2 (VIN), U18.3 (EN)
/PWR_3V3D/5V_SUPERCAP: C80.1, D22.2 (A), R76.2
/PWR_3V3D/STPD_3V3_BOOT: C72.1, U18.1 (BOOT)
/PWR_3V3D/STPD_3V3_COMP: C75.1, R73.1, U18.6 (COMP)
/PWR_3V3D/STPD_3V3_COMP_F: C76.1, R73.2
/PWR_3V3D/STPD_3V3_PH: C72.2, D20.1 (K), L3.1, U18.8 (PH)
/PWR_3V3D/STPD_3V3_SS: C77.1, U18.4 (SS)
/PWR_3V3D/STPD_3V3_VSENS: R72.2, R75.1, U18.5 (VSENSE)
/PWR_5VA_NEG5/+10V: C15.1, C16.1, C17.1, C18.1, C85.1, D3.1 (K), R18.1, U6.1 (IN), U6.2 (IN), U6.3 (EN/UV), U6.6 (PGFB), U20.5 (EN), U20.8 (IN)
/PWR_5VA_NEG5/INV_N5V5_COMP: C101.1, U21.1 (COMP)
/PWR_5VA_NEG5/INV_N5V5_FB: C91.1, R79.2, R81.1, U21.9 (FB)
/PWR_5VA_NEG5/INV_N5V5_FF: C91.2, R82.1
/PWR_5VA_NEG5/INV_N5V5_SW: D23.1 (K), L4.1, U21.6 (SW)
/PWR_5VA_NEG5/INV_N5V5_VIN: C89.1, R80.1, U21.3 (VIN)
/PWR_5VA_NEG5/INV_N5V5_VREF: C90.1, R79.1, U21.10 (VREF)
/PWR_5VA_NEG5/LDO_N5V_FB: C95.2, R83.2, R84.1, U22.3 (FB)
/PWR_5VA_NEG5/LDO_N5V_NR: C102.1, U22.14 (NR/SS)
/PWR_5VA_NEG5/LDO_P5V_FB: C86.2, R77.2, R78.1, U20.2 (FB)
/PWR_5VA_NEG5/LDO_P5V_NR: C88.1, U20.6 (NR/SS)
/PWR_5VA_NEG5/N5V5_PRE_N5VA: C93.1, C94.1, C97#2.1, C98.1, C99#2.1, C100.1, D23.2 (A), R81.2, R82.2, U21.8 (OUT), U22.13 (EN), U22.15 (IN), U22.16 (IN)
/PWR_9V_BRIDGE/BST_10V_FB: C15.2, R20.2, R22.1, U7.3 (FB)
/PWR_9V_BRIDGE/BST_10V_SW: D3.2 (A), L2.2, U7.1 (SW)
/PWR_9V_BRIDGE/LDO_9V_ILIM: R19.1, U6.5 (ILIM)
/PWR_9V_BRIDGE/LDO_9V_SET: C19.1, R21.1, U6.7 (SET)
/SENSOR_3AXIS_HMC100X/OFFSET_X+: C9.2, R11.2, RN1.5 (R4.2), U2.17 (OFFSET(+A))
/SENSOR_3AXIS_HMC100X/OFFSET_Y+: C12.2, R14.2, RN2.5 (R4.2), U2.15 (OFFSET+(B))
/SENSOR_3AXIS_HMC100X/OFFSET_Z+: C13.2, R17.2, RN3.5 (R4.2), U1.2 (OFFSET+)
/SENSOR_3AXIS_HMC100X/SETRESET_AFTER_1001: U1.3 (S/R-), U2.16 (S/R+(A))
/SENSOR_3AXIS_HMC100X/SETRESET_AFTER_1002A: U2.14 (S/R+(B)), U2.20 (S/R-(A))
/SENSOR_3AXIS_HMC100X/SETRESET_STRAP: C4.2, U1.1 (S/R+)
/SENSOR_OFFSET_DRIVERS/DAC_OUT_REF: RN1.1 (R1), RN2.1 (R1), RN3.1 (R1), U5.9 (VOUTD)
/SENSOR_OFFSET_DRIVERS/DAC_RDY_N: TP1.1, U5.5 (RDY/~BSY)
/SENSOR_OFFSET_DRIVERS/OFF_X_BN: Q5.1, R9.2
/SENSOR_OFFSET_DRIVERS/OFF_X_BP: Q6.1, R10.2
/SENSOR_OFFSET_DRIVERS/OFF_X_DRV: R9.1, R10.1, U4.1
/SENSOR_OFFSET_DRIVERS/OFF_X_INN: C9.1, RN1.3 (R2.2), U4.2 (-)
/SENSOR_OFFSET_DRIVERS/OFF_X_INP: C7.1, RN1.2 (R1.2), U4.3 (+)
/SENSOR_OFFSET_DRIVERS/OFF_X_SENSE_P: C7.2, Q5.3, Q6.3, R11.1, RN1.4 (R3.2)
/SENSOR_OFFSET_DRIVERS/OFF_Y_BN: Q7.1, R12.2
/SENSOR_OFFSET_DRIVERS/OFF_Y_BP: Q8.1, R13.2
/SENSOR_OFFSET_DRIVERS/OFF_Y_DRV: R12.1, R13.1, U4.7
/SENSOR_OFFSET_DRIVERS/OFF_Y_INN: C12.1, RN2.3 (R2.2), U4.6 (-)
/SENSOR_OFFSET_DRIVERS/OFF_Y_INP: C10.1, RN2.2 (R1.2), U4.5 (+)
/SENSOR_OFFSET_DRIVERS/OFF_Y_SENSE_P: C10.2, Q7.3, Q8.3, R14.1, RN2.4 (R3.2)
/SENSOR_OFFSET_DRIVERS/OFF_Z_BN: Q9.1, R15.2
/SENSOR_OFFSET_DRIVERS/OFF_Z_BP: Q10.1, R16.2
/SENSOR_OFFSET_DRIVERS/OFF_Z_DRV: R15.1, R16.1, U4.8
/SENSOR_OFFSET_DRIVERS/OFF_Z_INN: C13.1, RN3.3 (R2.2), U4.9 (-)
/SENSOR_OFFSET_DRIVERS/OFF_Z_INP: C11.1, RN3.2 (R1.2), U4.10 (+)
/SENSOR_OFFSET_DRIVERS/OFF_Z_SENSE_P: C11.2, Q9.3, Q10.3, R17.1, RN3.4 (R3.2)
/SENSOR_OFFSET_DRIVERS/UNUSED_LM324_CHD: U4.13 (-), U4.14
GND: C1.2, C2.2, C3.2, C6.2, C8.2, C14.2, C16.2, C17.2, C18.2, C19.2, C20.2, C21.2, C22.2, C23.2, C24.2, C25.2, C27.2, C28.2, C29.2, C30.2, C32.2, C33.2, C34.2, C35.2, C37.2, C38.2, C39.2, C40.2, C41.2, C42.2, C43.2, C44.2, C45.2, C46.2, C47.2, C48.2, C49.2, C50.2, C51.2, C52.2, C53.2, C54.2, C55.2, C56.2, C57.2, C58.2, C59.2, C60.2, C61.2, C63.2, C64.2, C65.2, C66.2, C67.2, C68.2, C69.2, C70.2, C71.2, C73.2, C74.2, C75.2, C76.2, C77.2, C78.2, C79.2, C80.2, C81.2, C82.2, C83.2, C84.2, C85.2, C87.2, C88.2, C89.2, C90.2, C92.2, C93.2, C94.2, C96.2, C96#2.2, C97.2, C97#2.2, C98.2, C98#2.2, C99.2, C99#2.2, C100.2, C101.2, C102.2, C103.1, C104.2, C105.2, C106.2, C107.2, C108.1, C109.2, C110.2, C111.1, C112.2, C113.2, D2.2 (A), D4.1 (A1), D5.1, D6.1, D7.1, D8.1, D9.1, D10.1, D11.1, D12.1, D13.1, D14.1, D15.1, D16.1, D17.1 (A1), D18.1, D19.1, D20.2 (A), H1.1, H2.1, H3.1, H4.1, H5#2.1, H6#2.1, H7#2.1, H8.1, J1.A1 (GND), J1.A12 (GND), J1.B1 (GND), J1.B12 (GND), J3.6 (VSS), J3.10 (SHIELD), J3.11 (VSS), J3.12 (VSS), J3.13 (VSS), J3.14 (VSS), L4.2, Q2.1 (S1), Q3.2, Q4.3 (E), Q11.2 (S), Q13.3 (D), R5.2, R7.2, R19.2, R21.2, R22.2, R41.2, R42.2, R43.1, R44.2, R45.2, R48.2, R49.2, R50.2, R53.2, R54.2, R55.2, R57.2, R60.2, R61.2, R65.2, R70.2, R71.2, R74.2, R75.2, R78.2, R84.2, R87.1, R89.2, R97.2, R98.2, R102.1, R103.2, R104.2, SW1.1, SW2.1, U1.4 (GND), U1.6 (OFFSET-), U2.1 (GND1(A)), U2.3 (OFFSET-(A)), U2.6 (GND2(A)), U2.7 (S/R-(B)), U2.8 (GND1(B)), U2.10 (OFFSET-(B)), U2.13 (GND2(B)), U2.18 (GND_PLN), U3.3 (GND), U3.7 (TP), U4.12 (+), U5.10 (VSS), U7.2 (GND), U8.1 (GND), U8.40 (GND), U8.41 (GND), U9.8 (GND), U10.5 (VCLAMP-), U10.17 (TP), U11.5 (VCLAMP-), U11.17 (TP), U12.5 (VCLAMP-), U12.17 (TP), U13.2 (SDx), U13.3 (SCx), U13.6 (GND), U13.7 (GND), U14.8 (GND), U15.8 (GND), U16.5 (AVSS1A), U16.7 (REF1-), U16.22 (DGND), U16.31 (XTAL1), U16.40 (AIN6-), U16.42 (REF2-), U16.44 (AVSS1B), U16.50 (AVSS2B), U16.53 (AVSS3), U16.56 (CLK_SEL), U16.60 (AVSS2A), U16.61 (AVSS4), U16.65 (EPAD(AVSSx)), U17.8 (GND), U18.7 (GND), U19.2 (GND), U19.5 (Pad), U20.3 (NC), U20.4 (GND), U20.9 (PwPd), U21.2 (GND), U21.7 (PSGND), U21.11 (PowerPAD), U22.7 (GND), U22.21 (EP), U23.2 (GND), U23.25 (GND), U24.27 (GND), U24.33 (GND), U25.4 (PORT), U25.12 (ENn_MUX), U25.13 (GND), U25.28 (GND), U25.29 (ENn_CC), U25.31 (GND), U26.A5, U26.A6, U26.A7, U26.A8, U26.B6, U26.B7, U26.B8, U26.MP1, U26.MP2, U26.MP3, U26.MP4, Y1.2 (GND), Y2.2, Y2.4
unnamed: C4.1, Q2.5 (D2), Q2.6 (D2), Q2.7 (D1), Q2.8 (D1)
unnamed: C6.1, R6.2
unnamed: C96.1, C97.1, C98#2.1, C99.1
unnamed: D1.2 (A), L1.2, U3.4 (SW)
unnamed: C5.2, D2.1 (K), Q4.1 (B), R8.2
unnamed: R96.1, U24.14 (LED)
unnamed: J2.A5 (CC1), R55.1
unnamed: J2.B5 (CC2), R54.1
unnamed: J2.A1 (GND), J2.A12 (GND), J2.B1 (GND), J2.B12 (GND)
unnamed: J3.5 (CLK), U23.3 (COM2)
unnamed: J3.3 (CMD), R94.2, U23.1 (COM1)
unnamed: J3.7 (DAT0), R93.2, U23.4 (COM3)
unnamed: J3.8 (DAT1), R92.2, U23.6 (COM4)
unnamed: J3.1 (DAT2), R91.2, U23.7 (COM5)
unnamed: J3.2 (DAT3), R90.2, U23.9 (COM6)
unnamed: Q1.1 (B), Q3.1, R2.2, R4.1
unnamed: C1.1, Q1.2 (C), Q2.3 (S2), R1.1, R2.1
unnamed: Q1.3 (E), Q2.4 (G2), Q3.3
unnamed: Q4.2 (C), R4.2
unnamed: C103.2, C104.1, Q12.3 (D), R87.2, U24.15 (VBUS)
unnamed: Q12.1 (G), R86.2
unnamed: Q13.1 (G), R88.2, R89.1
unnamed: Q13.2 (S), R85.2, R86.1
unnamed: R18.2, R20.1
unnamed: R6.1, U3.2 (COMP)
unnamed: R3.2, R7.1, U3.1 (FB)
unnamed: U6.8 (GND), U6.11 (GND)
unnamed: U8.19 (IO11), U9.14 (SER)
unnamed: U8.21 (IO13), U9.11 (SRCLK)
unnamed: U8.22 (IO14), U9.10 (~SRCLR)
unnamed: R29.1, U8.9 (IO16), U9.12 (RCLK)
unnamed: R28.1, U9.13 (~OE)
unnamed: R39.2, R41.1, TP2.1, U14.1 (EN/ULVO)
unnamed: R45.1, U14.9 (ILM)
unnamed: C45.1, U14.10 (ITIMER)
unnamed: R40.2, R42.1, U14.4 (PGTH)
unnamed: C46.1, U14.7 (dV/dt)
unnamed: R46.2, R48.1, TP3.1, U15.1 (EN/ULVO)
unnamed: R50.1, U15.9 (ILM)
unnamed: C50.1, U15.10 (ITIMER)
unnamed: R47.2, R49.1, U15.4 (PGTH)
unnamed: C51.1, U15.7 (dV/dt)
unnamed: U16.34 (~SYNC_OUT), U16.35 (~SYNC_IN)
unnamed: U23.8 (NO1), U24.21 (SD_CM)
unnamed: U23.10 (NO2), U24.20 (SD_CK)
unnamed: U23.12 (NO3), U24.19 (SD_D0)
unnamed: U23.14 (NO4), U24.18 (SD_D1)
unnamed: U23.15 (NO5), U24.23 (SD_D2)
unnamed: U23.13 (NO6), U24.22 (SD_D3)
unnamed: R102.2, U24.9 (RTERM)
unnamed: U24.4 (RXN), U25.10 (RXn)
unnamed: U24.5 (RXP), U25.9 (RXp)
unnamed: R100.2, R103.1, U24.29 (SD_CDZ)
unnamed: R101.2, R104.1, U24.28 (SD_WP)
unnamed: TP6.1, U24.12 (SPI_CK)
unnamed: R99.2, TP5.1, U24.13 (SPI_CS)
unnamed: TP7.1, U24.10 (SPI_MISO)
unnamed: TP8.1, U24.11 (SPI_MOSI)
unnamed: U24.1 (TXN), U25.7 (TXn)
unnamed: U24.2 (TXP), U25.6 (TXp)
unnamed: C112.1, U24.6 (X1), Y2.1
unnamed: C113.1, U24.7 (X2), Y2.3
